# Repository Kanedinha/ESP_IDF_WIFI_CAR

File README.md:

| Supported Targets | ESP32 |
| ----------------- | ----- |

Kanedinha's project
ESP_IDF_WIFI_CAR

RC CAR with wifi connection, using ESP32 WROVER Kit or WROOM Kit.

HLS (HTTP Live Streaming)
https://www.youtube.com/watch?v=Ea0JQh54amc

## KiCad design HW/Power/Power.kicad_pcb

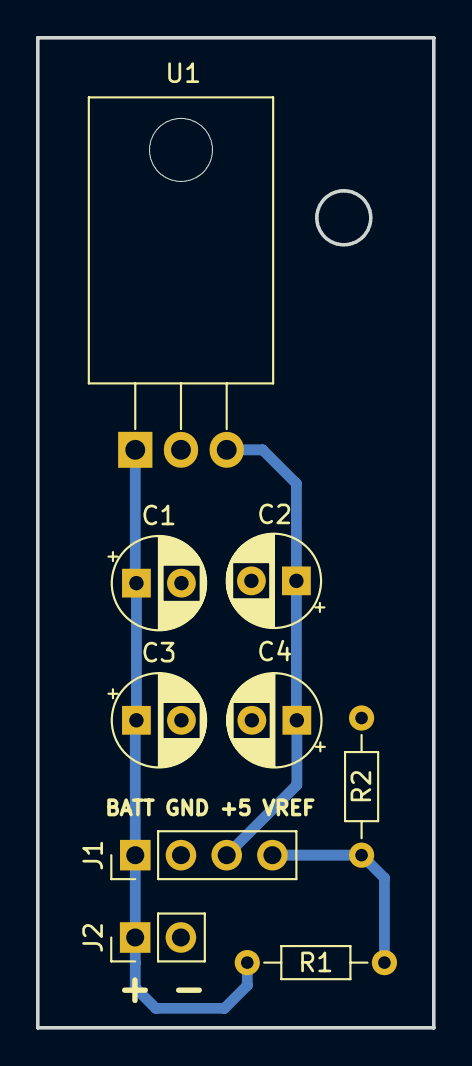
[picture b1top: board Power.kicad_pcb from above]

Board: 2 copper layers, 22.0 x 55.0 mm, 9 parts (0 on the bottom side), 4 nets.

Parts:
C1, C2: 10u; CP_Radial_D5.0mm_P2.50mm
C3, C4: 100u; CP_Radial_D5.0mm_P2.50mm
J1: Source; PinHeader_1x04_P2.54mm_Vertical
J2: Battery; PinHeader_1x02_P2.54mm_Vertical
R1, R2: 100k; R_Axial_DIN0204_L3.6mm_D1.6mm_P7.62mm_Horizontal
U1: L7805; TO-220-3_Horizontal_TabDown

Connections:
+5V: C2.1, C4.1, J1.3, U1.3 (OUT)
+BATT: C1.1, C3.1, J1.1, J2.1, R1.1, U1.1 (IN)
GND: C1.2, C2.2, C3.2, C4.2, J1.2, J2.2, R2.2, U1.2 (GND)
VDD: J1.4, R1.2, R2.1

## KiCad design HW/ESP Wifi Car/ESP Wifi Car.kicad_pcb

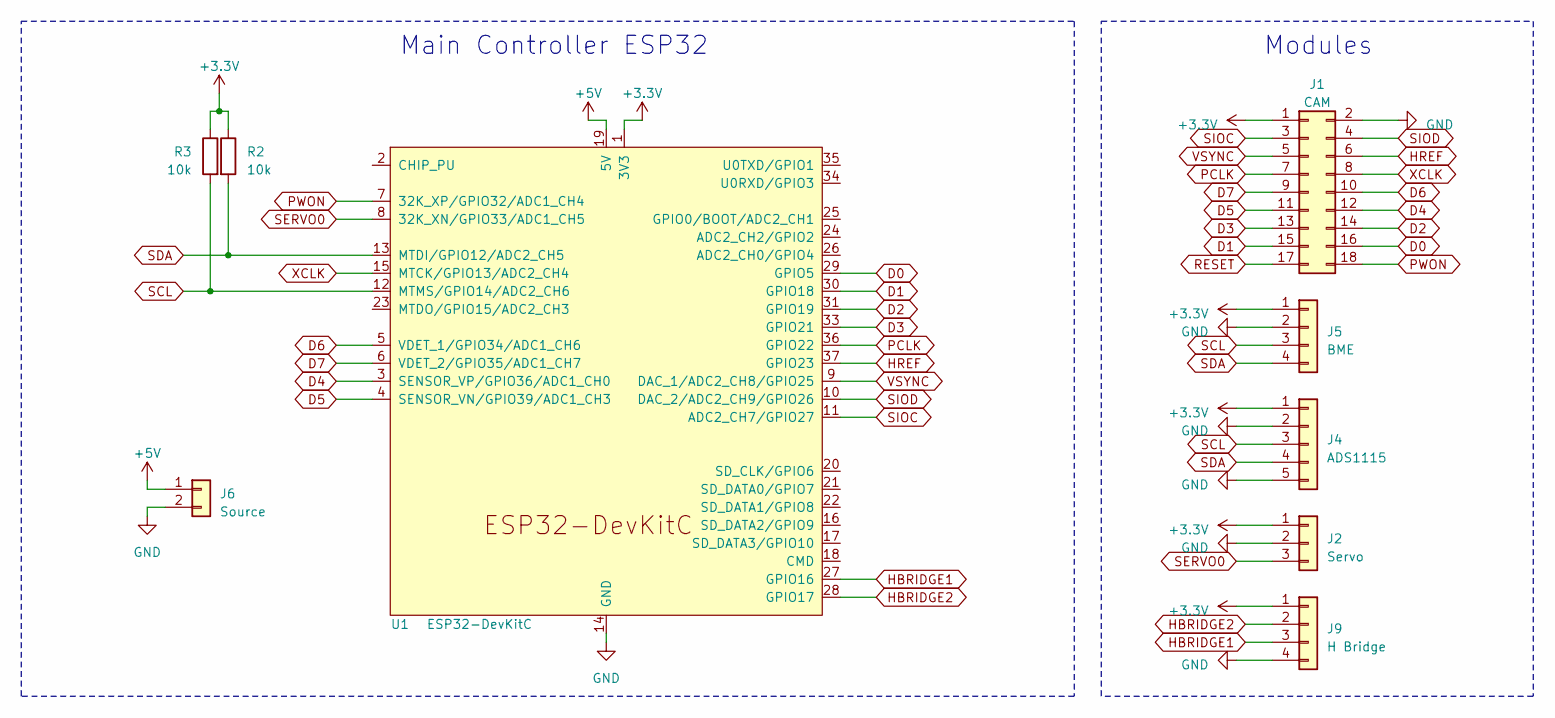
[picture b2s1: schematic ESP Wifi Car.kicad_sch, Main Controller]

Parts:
J1: CAM; PinHeader_2x09_P2.54mm_Vertical
J2: Servo; PinHeader_1x03_P2.54mm_Vertical
J4: ADS1115; PinHeader_1x05_P2.54mm_Vertical
J5: BME; PinHeader_1x04_P2.54mm_Vertical
J6: Source; PinHeader_1x02_P2.54mm_Vertical
J9: H Bridge; PinHeader_1x04_P2.54mm_Vertical
R2, R3: 10k; R_Axial_DIN0204_L3.6mm_D1.6mm_P7.62mm_Horizontal
U1: ESP32-DevKitC

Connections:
+3.3V: J1.1, J2.1, J4.1, J5.1, J9.1, R2.1, R3.1, U1.1 (3V3)
+5V: J6.1, U1.19 (5V)
D0: J1.16, U1.29 (GPIO5)
D1: J1.15, U1.30 (GPIO18)
D2: J1.14, U1.31 (GPIO19)
D3: J1.13, U1.33 (GPIO21)
D4: J1.12, U1.3 (SENSOR_VP/GPIO36/ADC1_CH0)
D5: J1.11, U1.4 (SENSOR_VN/GPIO39/ADC1_CH3)
D6: J1.10, U1.5 (VDET_1/GPIO34/ADC1_CH6)
D7: J1.9, U1.6 (VDET_2/GPIO35/ADC1_CH7)
GND: J1.2, J2.2, J4.2, J4.5, J5.2, J6.2, J9.4, U1.14 (GND), U1.32 (GND), U1.38 (GND)
HBRIDGE1: J9.3, U1.27 (GPIO16)
HBRIDGE2: J9.2, U1.28 (GPIO17)
HREF: J1.6, U1.37 (GPIO23)
PCLK: J1.7, U1.36 (GPIO22)
PWON: J1.18, U1.7 (32K_XP/GPIO32/ADC1_CH4)
RESET: J1.17
SCL: J4.3, J5.3, R3.2, U1.12 (MTMS/GPIO14/ADC2_CH6)
SDA: J4.4, J5.4, R2.2, U1.13 (MTDI/GPIO12/ADC2_CH5)
SERVO0: J2.3, U1.8 (32K_XN/GPIO33/ADC1_CH5)
SIOC: J1.3, U1.11 (ADC2_CH7/GPIO27)
SIOD: J1.4, U1.10 (DAC_2/ADC2_CH9/GPIO26)
VSYNC: J1.5, U1.9 (DAC_1/ADC2_CH8/GPIO25)
XCLK: J1.8, U1.15 (MTCK/GPIO13/ADC2_CH4)

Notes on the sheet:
Main Controller ESP32
Modules

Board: 2 copper layers, 9 parts (0 on the bottom side), 23 nets, no tracks yet.

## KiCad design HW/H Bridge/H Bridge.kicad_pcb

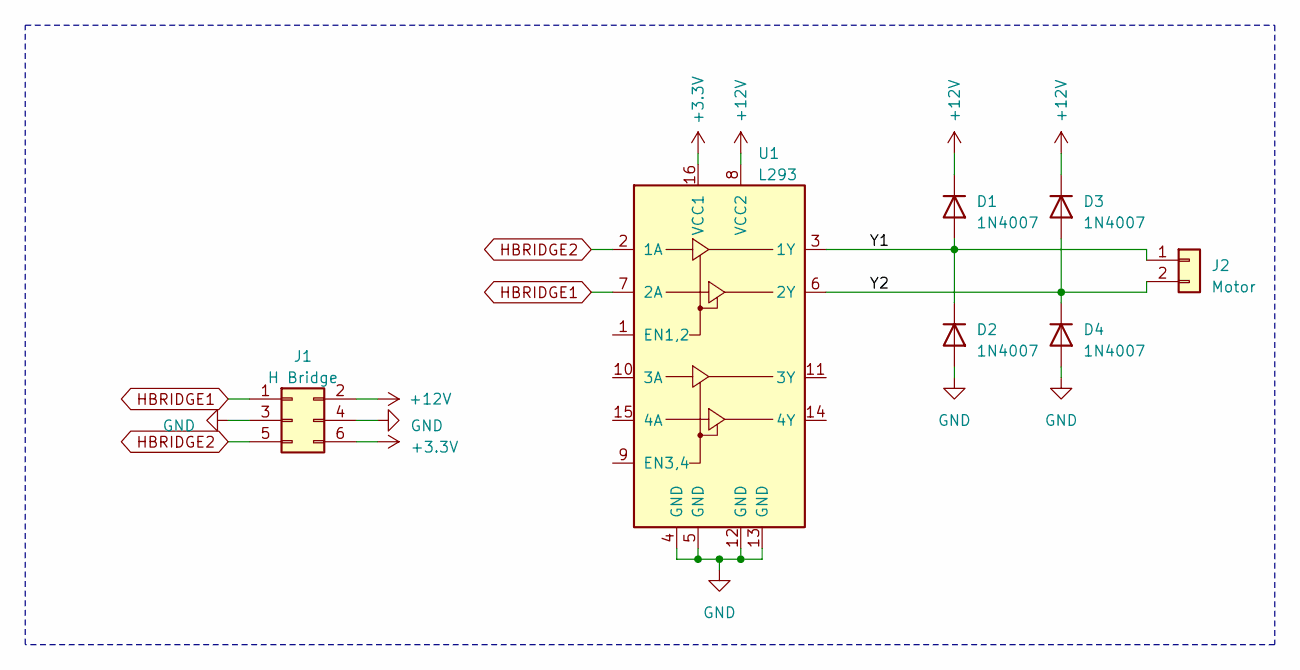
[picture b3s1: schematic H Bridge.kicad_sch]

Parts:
D1, D2, D3, D4: 1N4007; D_DO-41_SOD81_P10.16mm_Horizontal
J1: H Bridge; PinHeader_2x03_P2.54mm_Vertical
J2: Motor; PinHeader_1x02_P2.54mm_Vertical
U1: L293; DIP-16_W7.62mm

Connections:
+3.3V: J1.6, U1.16 (VCC1)
+12V: D1.1 (K), D3.1 (K), J1.2, U1.8 (VCC2)
/Y1: D1.2 (A), D2.1 (K), J2.1, U1.3 (1Y)
/Y2: D3.2 (A), D4.1 (K), J2.2, U1.6 (2Y)
GND: D2.2 (A), D4.2 (A), J1.3, J1.4, U1.4 (GND), U1.5 (GND), U1.12 (GND), U1.13 (GND)
HBRIDGE1: J1.1, U1.7 (2A)
HBRIDGE2: J1.5, U1.2 (1A)

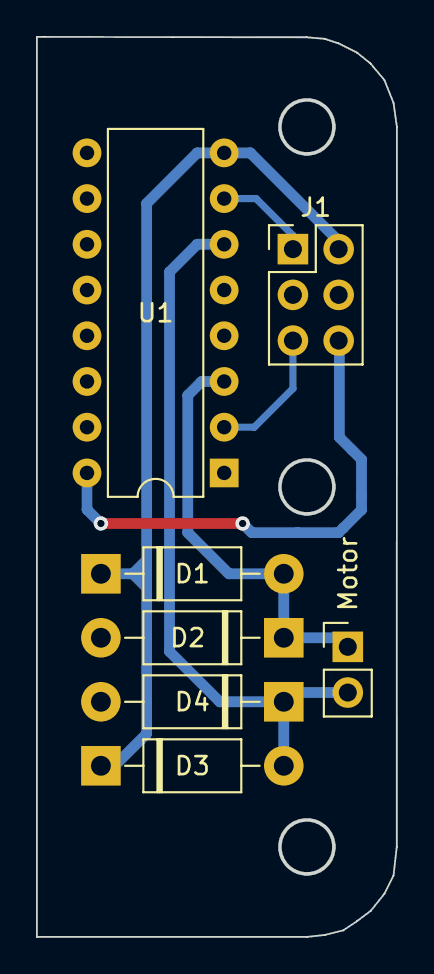
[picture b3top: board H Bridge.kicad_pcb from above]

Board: 2 copper layers, 19.9 x 49.9 mm, 7 parts (0 on the bottom side), 7 nets.

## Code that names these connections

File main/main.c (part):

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{
    camera_config.pin_pwdn = 21;
    camera_config.pin_reset = -1;
    camera_config.pin_xclk = 13;
    camera_config.pin_sccb_sda = 12;
    camera_config.pin_sccb_scl = 14;

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    camera_config.pin_d1 = 39;
    camera_config.pin_d0 = 36;

    camera_config.pin_vsync = 27;
    camera_config.pin_href = 23;
    camera_config.pin_pclk = 22;
    camera_config.xclk_freq_hz = 4000000;

    camera_config.ledc_timer = LEDC_TIMER_0;
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
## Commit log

2023-01-20 Create ex
2023-01-20 Create exclude
2023-01-25 my first commit
2023-01-25 teste
2023-01-25 JQuery com problema
2023-01-26 click&hold event js
2023-01-26 ajax dont send info
2023-01-27 Now JSON send
2023-01-27 servo cys s0009 wtf?
2023-01-30 change iot_servo -> PWM
2023-01-30 Httpd response, how i do this?
2023-01-31 Adjust to ULN2003 with defines and clean the code
2023-02-01 multiple buttons for step, AS5600 with I2C
2023-02-02 steps OK
2023-02-02 how i read lvl.txt?
2023-02-03 BME280 is working
2023-02-07 nhaaaaaa
2023-02-14 bat lvl OK
2023-02-14 speed bug ajusted
2023-02-15 CAM OV7670 begining code
2023-02-15 CAM without pins define
2023-02-16 cam test
2023-02-17 have something in response
2023-02-20 check the commit after
2023-02-20 gitgit
2023-02-22 gitignore all trashs please
2023-02-22 handshake doesn't made
2023-02-23 web socket opened, but WS header fail
2023-02-23 wtf?????
2023-02-24 comunication speed is too slow
2023-02-24 keep trying
2023-02-27 home test
2023-02-27 why camera can caopture randonly ?
2023-02-28 NOW WE HAVE IMAGE
2023-02-28 4MHz work, but more clock not work
2023-02-28 need to interpreter image as binary in JS
2023-03-01 10 FPS! but in the JS is too slow
2023-03-02 dale
2023-03-03 NHAAAAAA works with QVGA 10MHz
2023-03-06 cam with ADS1115 I2C
2023-03-06 adjust the style and implement other I2C devices
2023-03-07 fps > 20 with qvga and grayscale
2023-03-08 JPEG lib
2023-03-09 QVGA RGB565 arrive 7 ~9 average fps
2023-04-30 Temp and BatLvL working in tasks
2023-04-30 working
2023-05-04 why gpio have problem?
2023-05-04 commmirt
2023-05-04 Hardware add
    3 PCB's are maded to make the little car kanedístico
2023-05-04 PCB's OK: power, H Bridge driver
2023-05-05 zdfshgarsdhar
2023-05-09 Update .gitignore
    build files add to ignore
2023-05-10 work for SO is working
2023-05-11 wifi with router
2023-12-30 out somethings
